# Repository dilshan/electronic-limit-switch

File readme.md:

## Electronic Limit Switch

This is an open-source fluid level control module designed for reliable and automated liquid management in tanks.

## Overview

This module can utilize two float-type limit switches or electronic sensor switches to detect fluid levels and control a relay accordingly. A microcontroller implements hysteresis logic to avoid unnecessary relay toggling caused by minor fluid level fluctuations, which enhances the system's reliability and lifespan.

## How it works

1. The module monitors two limit switches:
   - *Upper limit switch (J1)*: Closes when the fluid level falls below the upper threshold.
   - *Lower limit switch (J2)*: Closes when the fluid level rises above the lower threshold.

2. Based on these inputs, the onboard microcontroller:
   - Activates or deactivates the relay.
   - Applies hysteresis logic to prevent rapid toggling.

3. The *J4 terminal block* provides:
   - AC mains input (up to 240V).
   - Relay output for controlling pumps or other devices.

## License

This is a [certified open-source hardware project](https://certification.oshwa.org/lk000017.html). All [design files](https://github.com/dilshan/electronic-limit-switch/tree/main/design), [documentation](https://github.com/dilshan/electronic-limit-switch/wiki), and [firmware source code](https://github.com/dilshan/electronic-limit-switch/tree/main/firmware) are available for download at the project source repository. The content of this project is distributed under the following licenses:

- Hardware license: [CERN-OHL-W](https://opensource.org/license/cern-ohl-w)
- Software license: [MIT License](https://github.com/dilshan/electronic-limit-switch?tab=MIT-1-ov-file)
- Documentation license: [CC BY 4.0](https://creativecommons.org/licenses/by/4.0)

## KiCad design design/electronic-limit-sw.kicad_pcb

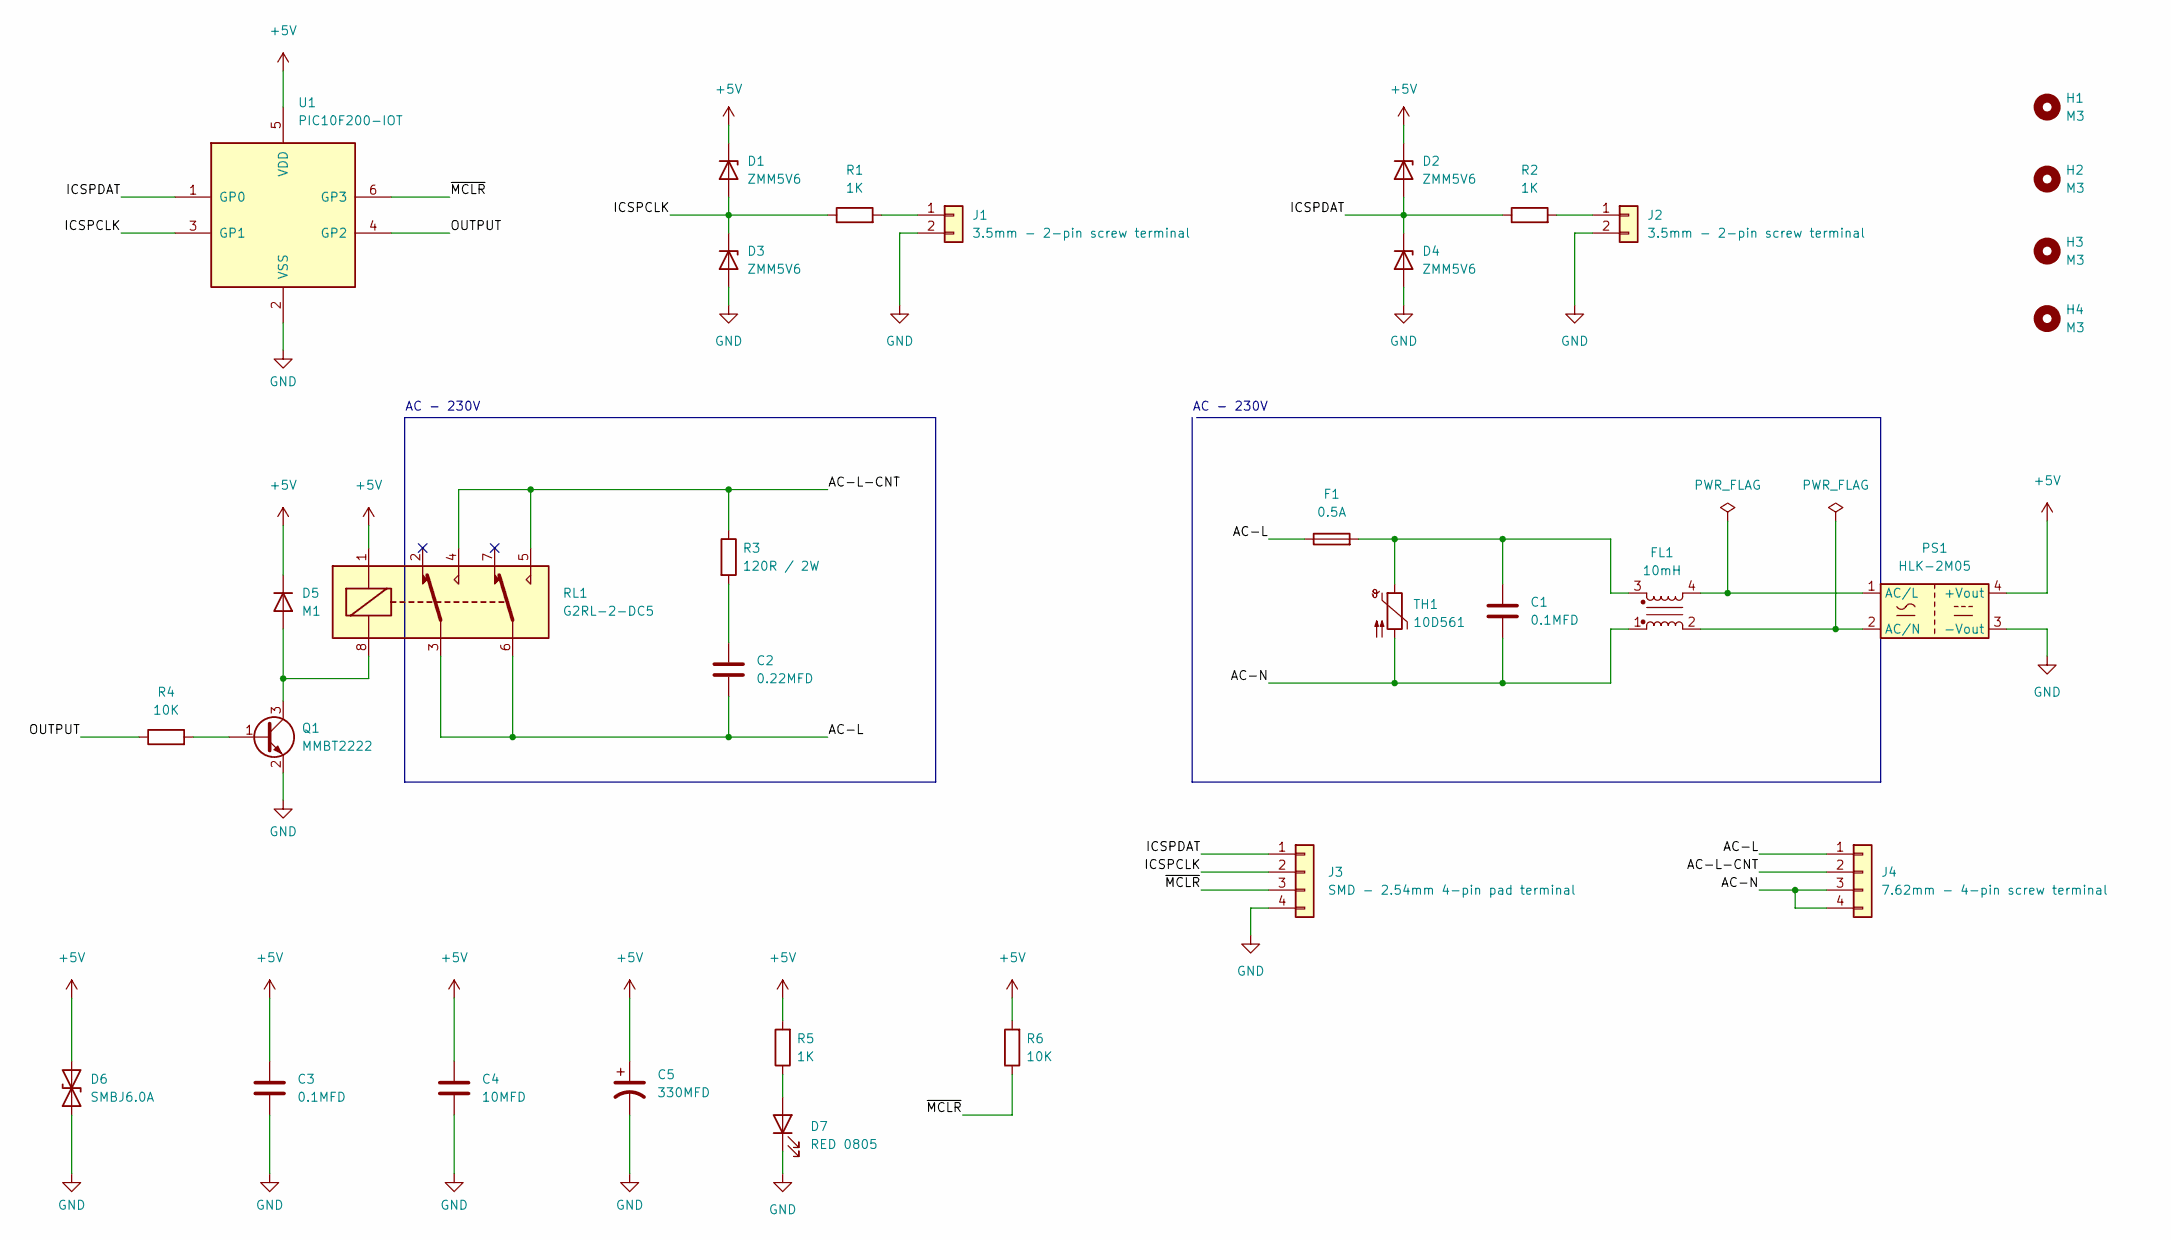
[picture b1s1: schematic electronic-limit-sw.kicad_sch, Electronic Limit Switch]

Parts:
C1: 0.1MFD; C_Rect_L11.0mm_W4.3mm_P10.00mm_MKT
C2: 0.22MFD; C_Rect_L11.0mm_W5.1mm_P10.00mm_MKT
C3: 0.1MFD; C_0603_1608Metric_Pad1.08x0.95mm_HandSolder
C4: 10MFD; C_0805_2012Metric_Pad1.18x1.45mm_HandSolder
C5: 330MFD; CP_Elec_6.3x7.7
D1, D2, D3, D4: ZMM5V6; D_MiniMELF_Handsoldering
D5: M1; D_SMA_Handsoldering
D6: SMBJ6.0A; D_SMB_Handsoldering
D7: RED 0805; LED_0805_2012Metric_Pad1.15x1.40mm_HandSolder
F1: 0.5A; Fuse_Littelfuse_372_D8.50mm
FL1: 10mH; CM-Choke-15.5mmx10.9mm
H1, H2, H3, H4: M3; MountingHole_3.5mm
J1, J2: 3.5mm - 2-pin screw terminal; PhoenixContact_MCV_1,5_2-G-3.5_1x02_P3.50mm_Vertical
J3: SMD - 2.54mm 4-pin pad terminal; pogo-2.54mmx4
J4: 7.62mm - 4-pin screw terminal; Screw-Terminal-4Way-7.62mm
PS1: HLK-2M05; PSU-Module-10.5mmx16.5mm
Q1: MMBT2222; SOT-23-3
R1, R2, R5: 1K; R_0603_1608Metric_Pad0.98x0.95mm_HandSolder
R3: 120R / 2W; R_Axial_DIN0516_L15.5mm_D5.0mm_P20.32mm_Horizontal
R4, R6: 10K; R_0603_1608Metric_Pad0.98x0.95mm_HandSolder
RL1: G2RL-2-DC5; Relay_DPDT_Omron_G2RL
TH1: 10D561; RV_Disc_D12mm_W4.2mm_P7.5mm
U1: PIC10F200-IOT; SOT-23-6

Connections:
+5V: C3.1, C4.1, C5.1, D1.1 (K), D2.1 (K), D5.1 (K), D6.2 (A2), PS1.4 (+Vout), R5.2, R6.2, RL1.1, U1.5 (VDD)
/AC-L: C2.2, F1.1, J4.1, RL1.3, RL1.6
/AC-L-CNT: J4.2, R3.1, RL1.4, RL1.5
/AC-N: C1.2, FL1.1, J4.3, J4.4, TH1.2
/ICSPCLK: D1.2 (A), D3.1 (K), J3.2, R1.1, U1.3 (GP1)
/ICSPDAT: D2.2 (A), D4.1 (K), J3.1, R2.1, U1.1 (GP0)
/OUTPUT: R4.1, U1.4 (GP2)
/~MCLR: J3.3, R6.1, U1.6 (GP3)
GND: C3.2, C4.2, C5.2, D3.2 (A), D4.2 (A), D6.1 (A1), D7.1 (K), J1.2, J2.2, J3.4, PS1.3 (-Vout), Q1.2 (E), U1.2 (VSS)
unnamed: C1.1, F1.2, FL1.3, TH1.1
unnamed: C2.1, R3.2
unnamed: D5.2 (A), Q1.3 (C), RL1.8
unnamed: D7.2 (A), R5.1
unnamed: J1.1, R1.2
unnamed: J2.1, R2.2
unnamed: FL1.4, PS1.1 (AC/L)
unnamed: FL1.2, PS1.2 (AC/N)
unnamed: Q1.1 (B), R4.2

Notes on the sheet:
AC - 230V

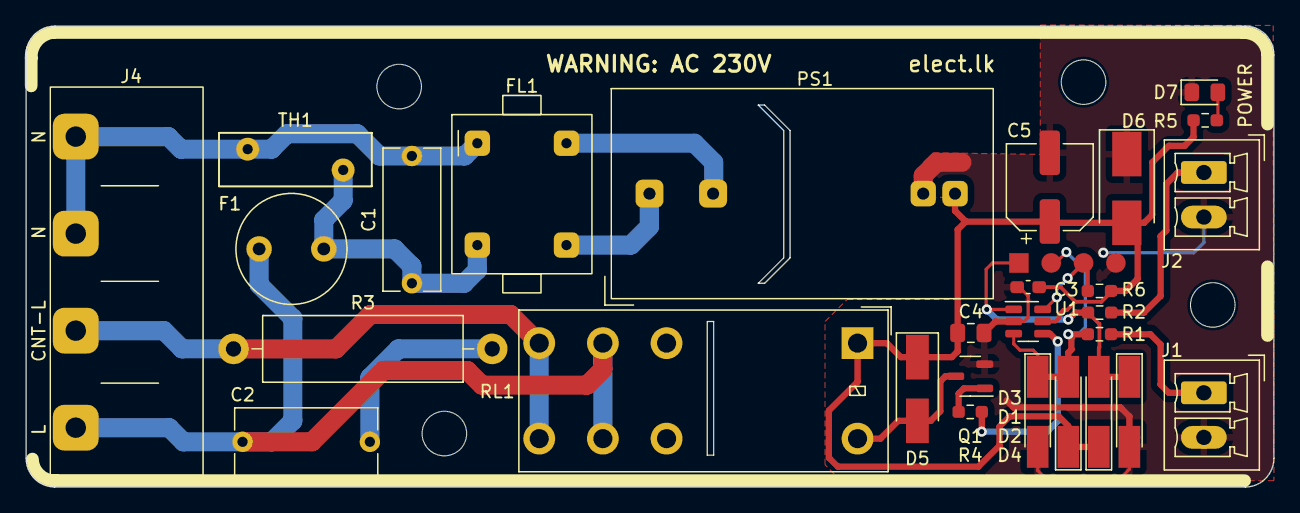
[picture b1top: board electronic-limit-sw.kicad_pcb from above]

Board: 2 copper layers, 98.0 x 36.2 mm, 33 parts (0 on the bottom side), 18 nets.

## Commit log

2024-01-12 Add new Simtelic logo and update version.
2024-01-12 Add gerber files for production [12/01/2024]
2024-06-21 Add initial version of documentation.
2025-07-01 Upgrade project to new KiCAD version.
2025-07-02 Add LICENSE file.
2025-07-02 Add license into source code. Add mini readme file for the firmware directory.
2025-07-02 Update readme file in firmware section with more details.
2025-07-06 Add resources related to documentation.
2025-07-06 Add schematic in PDF format.
2025-07-06 Add initial version of readme file.
2025-07-06 Add Wiki and repo links into the readme file.
2025-07-06 Add picture of prototype build into readme file.
2025-07-06 Minor updates in readme file.
2025-07-06 Add build output directories into gitignore.
2025-07-18 Add OSHWA certification data and graphics.
